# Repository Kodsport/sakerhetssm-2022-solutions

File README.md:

# sakerhetssm-2022

Uppgifter till Säkerhets-SM 2022

I det här repot hittar du källkoden till alla uppgifter från Säkerhets-SM 2022, inklusive dommarlösningar och vissa writeups.

Alla nerladdningsbara uppgiftsfiler ligger i respektive uppgiftsmappar. Uppgifter som hade services har också en `docker-compose.yml` fil som låter er starta uppgifterna lokalt. För att göra det, installera [Docker](https://docs.docker.com/get-docker/) samt [docker-compose](https://docs.docker.com/compose/install/) och kör `docker-compose up` i uppgiftsmappen. Anslut sedan till `127.0.0.1:50000`.

## Lösningsstream

<!-- Calle Svensson har streamat när han löser uppgifter från kvalet:

- Del 1 - https://www.youtube.com/watch?v=TzcGTrwnIvc
- Del 2 - https://www.youtube.com/watch?v=_Ki1XHeZ_JM -->

Några uppgifter gicks även igenom på kvalets avslutningsstream: <https://youtu.be/cFJCb-_NIes>

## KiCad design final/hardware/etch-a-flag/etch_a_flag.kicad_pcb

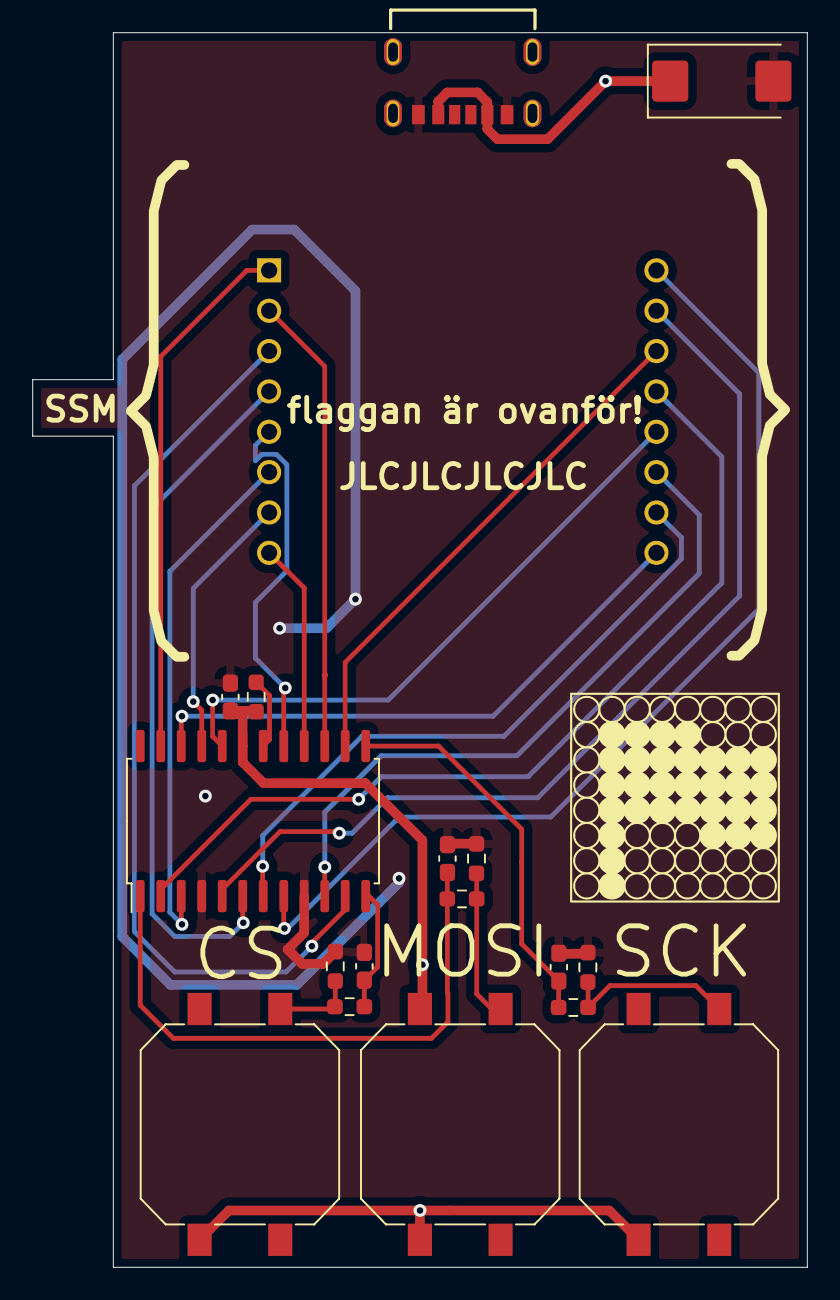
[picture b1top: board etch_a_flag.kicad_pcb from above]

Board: 2 copper layers, 48.0 x 76.5 mm, 18 parts (0 on the bottom side), 25 nets.

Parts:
C1, C2, C3, C6: 100n; C_0603_1608Metric_Pad1.08x0.95mm_HandSolder
C5: 100u; CP_EIA-7343-43_Kemet-X_Pad2.25x2.55mm_HandSolder
DS1: TA08-81GWA; 8x8_1.25_dot_matrix
J1: USB_C_Receptacle_USB2.0; GCT_USB4125-GF-A_REVA2
R1: 60k; R_0603_1608Metric_Pad0.98x0.95mm_HandSolder
R2, R3, R4, R5, R6, R7: 1k; R_0603_1608Metric_Pad0.98x0.95mm_HandSolder
SW_CK1: SW_Push; SW_Push_1P1T_NO_CK_PTS125Sx43PSMTR
SW_CS3: SW_Push; SW_Push_1P1T_NO_CK_PTS125Sx43PSMTR
SW_MOSI2: SW_Push; SW_Push_1P1T_NO_CK_PTS125Sx43PSMTR
U2: MAX7219; SOP-24_7.5x15.4mm_P1.27mm

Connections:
CS: C3.1, R7.2, U2.12 (LOAD)
GND: C1.2, C2.2, C3.2, C5.2, C6.1, J1.A12 (GND), J1.B12 (GND), R2.2, R4.2, R6.2, U2.4 (GND), U2.9 (GND)
MOSI: C2.1, R5.2, U2.1 (DIN)
unnamed: R1.1, U2.18 (ISET)
unnamed: R2.1, R3.1, SW_CK1.1
unnamed: R4.1, R5.1, SW_MOSI2.1
unnamed: R6.1, R7.1, SW_CS3.1
SCK: C1.1, R3.2, U2.13 (CLK)
VCC: C5.1, C6.2, J1.A9 (VBUS), J1.B9 (VBUS), R1.2, SW_CK1.2, SW_CS3.2, SW_MOSI2.2, U2.19 (V+)
c1: DS1.9, U2.22 (SEG_DP)
c2: DS1.14, U2.14 (SEG_A)
c3: DS1.8, U2.16 (SEG_B)
c4: DS1.12, U2.20 (SEG_C)
c5: DS1.1, U2.23 (SEG_D)
c6: DS1.7, U2.21 (SEG_E)
c7: DS1.2, U2.15 (SEG_F)
c8: DS1.5, U2.17 (SEG_G)
r1: DS1.13, U2.2 (DIG_0)
r2: DS1.3, U2.11 (DIG_1)
r3: DS1.4, U2.6 (DIG_2)
r4: DS1.10, U2.7 (DIG_3)
r5: DS1.6, U2.3 (DIG_4)
r6: DS1.11, U2.10 (DIG_5)
r7: DS1.15, U2.5 (DIG_6)
r8: DS1.16, U2.8 (DIG_7)

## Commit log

2022-04-01 kval uppgifter
2022-06-12 final challs
2022-10-20 våffelhuset
